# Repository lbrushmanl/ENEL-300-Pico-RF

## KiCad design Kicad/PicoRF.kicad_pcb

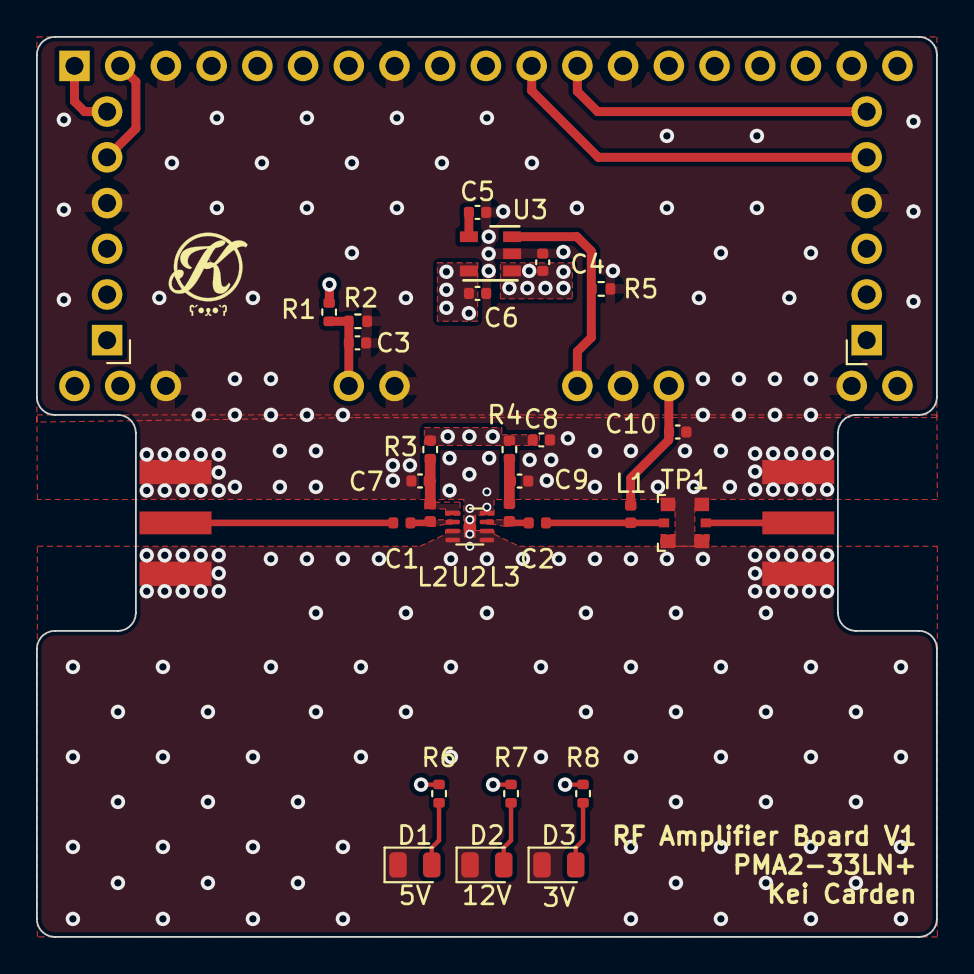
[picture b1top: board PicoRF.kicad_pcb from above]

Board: 4 copper layers, 50.0 x 50.0 mm, 32 parts (1 on the bottom side), 22 nets.

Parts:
C1, C2: 100p; C_0402_1005Metric
C3, C5: 10n; C_0402_1005Metric
C4: 1u; C_0402_1005Metric
C6: 10u; C_0402_1005Metric
C7, C8: 4u7; C_0402_1005Metric
C9: 33p; C_0402_1005Metric
C10: 1n; C_0402_1005Metric
D1: 5V-LED; LED_0805_2012Metric
D2: 12V-LED; LED_0805_2012Metric
D3: 3V-LED; LED_0805_2012Metric
J1: IN; SMA_Male
J2: OUT; SMA_Female
J3: IN; PinHeader_1x06_P2.54mm_Horizontal
J4: OUT; PinSocket_1x06_P2.54mm_Horizontal
L1: 47n; L_0402_1005Metric
L2, L3: 33n; L_0402_1005Metric
R1: 30k; R_0402_1005Metric
R2, R5: 10k; R_0402_1005Metric
R3: 4k02; R_0402_1005Metric
R4: 10R; R_0402_1005Metric
R6: 150; R_0402_1005Metric
R7: 499; R_0402_1005Metric
R8: 47; R_0402_1005Metric
TP1: MM8130-2600
U1: Pico
U2: PMA2-33LN+; MC1631-1-8-1EP_2x2mm_P0.5mm
U3: TAR5SB30; SSOP5-P-0.95

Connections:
/Microcontroller/CTRL: R5.1, U1.29 (GPIO22), U3.3 (CTRL)
/Microcontroller/IN.5V: J3.1, J4.1, R6.2, U1.39 (VSYS)
/Microcontroller/IN.RX: J3.5, U1.2 (GPIO1)
/Microcontroller/IN.TX: J3.6, U1.1 (GPIO0)
/Microcontroller/OUT.RX: J4.6, U1.12 (GPIO9)
/Microcontroller/OUT.TX: J4.5, U1.11 (GPIO8)
/Microcontroller/TEST: C10.1, L1.2, U1.27 (GPIO21)
/Microcontroller/V_{measured}: C3.1, R1.2, R2.1, U1.34 (GPIO28_ADC2)
/RF Component/LNA-PWR: C7.2, L2.1, R3.2, U2.1 (V+)
/RF Component/NOISE: C5.1, U3.4 (NOISE)
/RF Component/OUT.3V: C6.1, C8.1, R3.1, R4.1, R8.1, U3.5 (Vout)
/RF Component/REG.12V: C4.1, J3.2, J3.3, J4.2, J4.3, R1.1, R7.2, U3.1 (Vin)
/RF Component/RF_{IN}: C1.2, L2.2, U2.2 (IN)
/RF Component/RF_{OUT}: C2.1, L3.2, U2.7 (OUT)
/RFIN1: C1.1, J1.1 (In)
/RFOUT1: C2.2, L1.1, TP1.1 (IN)
GND: C3.2, C4.2, C5.2, C6.2, C7.1, C8.2, C9.2, C10.2, D1.1 (K), D2.1 (K), D3.1 (K), J1.2 (Ext), J2.2 (Ext), J3.4, J4.4, R2.2, R5.2, TP1.3 (GND), U1.3 (GND), U1.8 (GND), U1.13 (GND), U1.18 (GND), U1.23 (GND), U1.28 (GND), U1.33 (AGND), U1.38 (GND), U2.3 (NC), U2.4 (NC), U2.5 (NC), U2.6 (NC), U2.8 (NC), U2.P (NC), U3.2 (GND)
unnamed: C9.1, L3.1, R4.2
unnamed: D1.2 (A), R6.1
unnamed: D2.2 (A), R7.1
unnamed: D3.2 (A), R8.2
unnamed: J2.1 (In), TP1.2 (OUT)

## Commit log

2023-04-27 Adding repo
